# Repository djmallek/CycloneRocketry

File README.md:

# Cyclone Rocketry

This is an avionics control board for Iowa State's Cyclone Rocketry club. Our rocketry must carry a payload to a target altitude of 10,000ft.  Score is determined by how close a team's rocket can get to the target altitude, among other things.  To ensure we hit our target altitude, we have an air brakes system which actively calculates when and how long it needs to deploy it's air brakes system.  The board additionally provides data-logging and radio-relayed GPS tracking.

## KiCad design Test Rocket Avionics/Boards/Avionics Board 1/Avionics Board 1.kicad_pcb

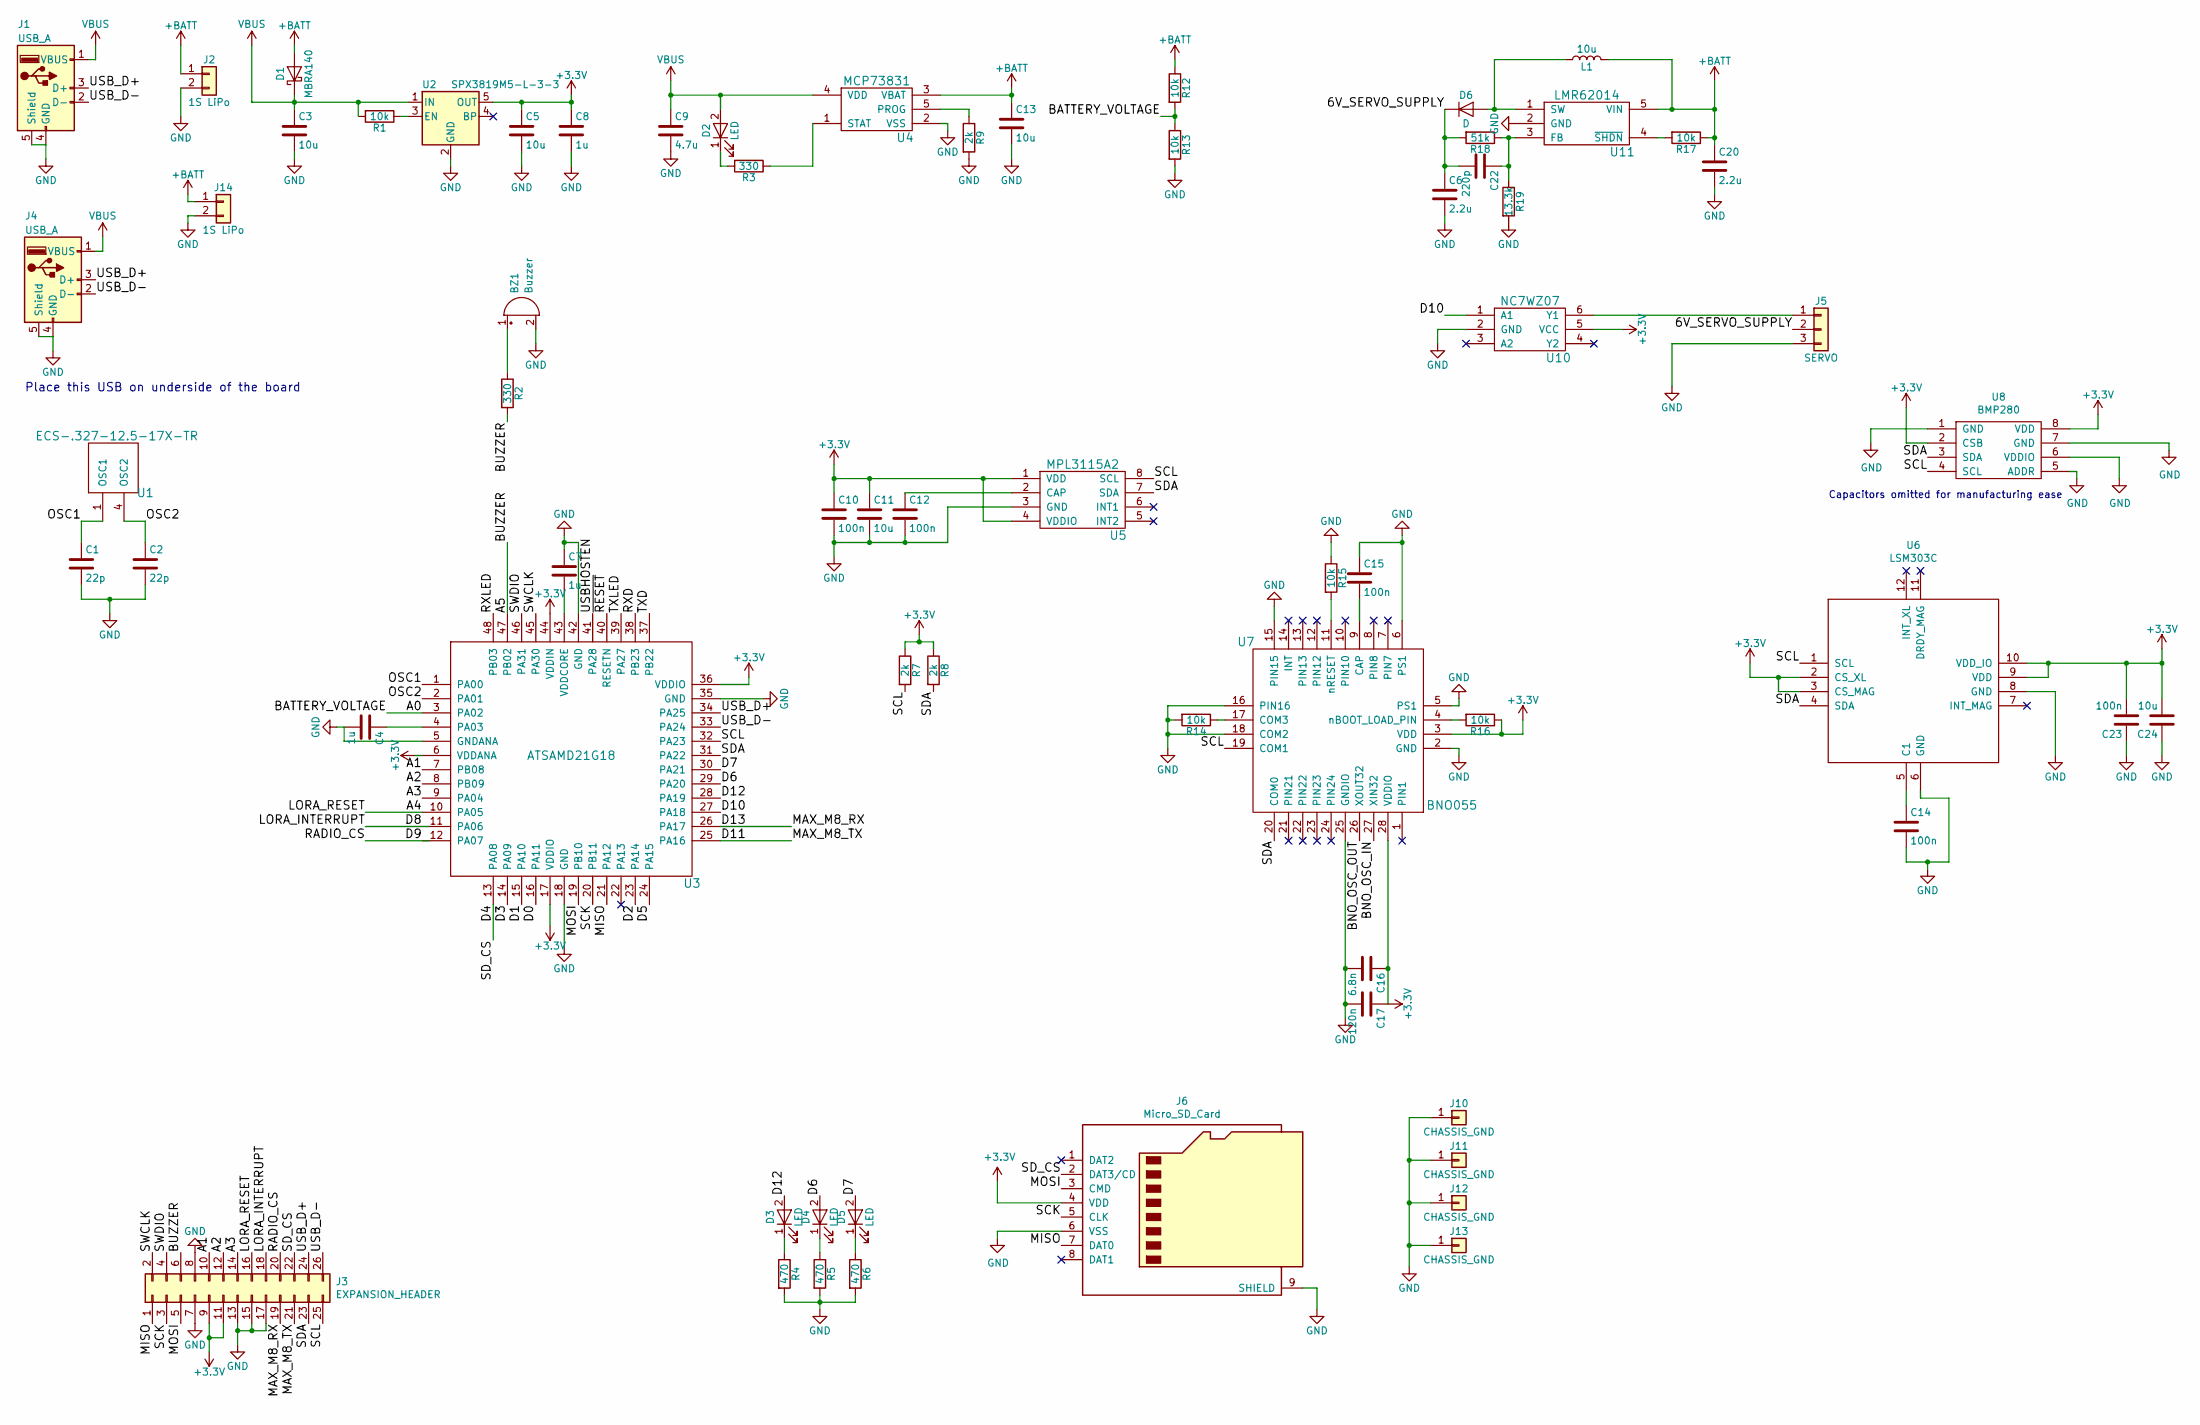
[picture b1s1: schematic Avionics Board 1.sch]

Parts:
BZ1: Buzzer; CUI_CMT-5023S-SMT
C1, C2: 22p; C_0805
C3, C5, C11, C13, C24: 10u; C_1206
C4, C7, C8: 1u; C_0805
C6, C20: 2.2u; C_1206
C9: 4.7u; C_1206
C10, C12, C14, C15, C23: 100n; C_0805
C16: 6.8n; C_0805
C17: 120n; C_0805
C22: 220p; C_0805
D1: MBRA140; DO-214AC
D2, D3, D4, D5: LED; D_0603
D6: D; D_SOD-123F
J1, J4: USB_A; USB_Mini-B
J2: 1S LiPo; JST-PH2
J3: EXPANSION_HEADER; Pin_Header_Straight_2x13_Pitch1.00mm
J5: SERVO; Pin_Header_Straight_1x03_Pitch2.54mm
J6: Micro_SD_Card; MicroSD_DM3D-SF
J10, J11, J12, J13: CHASSIS_GND; MountingHole_2.7mm_M2.5_Pad
J14: 1S LiPo; Pin_Header_Straight_1x02_Pitch2.54mm
L1: 10u; L_Wuerth_HCI-5040
R1, R12, R13, R14, R15, R16, R17: 10k; R_0805
R2, R3: 330; R_0805
R4, R5, R6: 470; R_0805
R7, R8, R9: 2k; R_0805
R18: 51k; R_0805
R19: 13.3k; R_0805
U1: ECS-.327-12.5-17X-TR; XC1195CT-ND
U2: SPX3819M5-L-3-3; SOT-23-5
U3: ATSAMD21G18; TQFP-48_7x7mm_Pitch0.5mm
U4: MCP73831; TSOT-23-5
U5: MPL3115A2
U6: LSM303C; LGA-12_2x2mm_Pitch0.5mm
U7: BNO055; BNO055-LGA
U8: BMP280
U10: NC7WZ07; SOT-363_SC-70-6
U11: LMR62014; SOT-23-5

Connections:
+3V3: C5.1, C8.1, C10.1, C11.1, C16.1, C17.1, C23.2, C24.2, J3.9, J3.11, J6.4 (VDD), R7.1, R8.1, R16.1, U2.5 (OUT), U3.6 (VDDANA), U3.17 (VDDIO), U3.36 (VDDIO), U3.44 (VDDIN), U5.1 (VDD), U5.4 (VDDIO), U6.2 (CS_XL), U6.3 (CS_MAG), U6.9 (VDD), U6.10 (VDD_IO), U7.3 (VDD), U7.28 (VDDIO), U8.2 (CSB), U8.8 (VDD), U10.5 (VCC)
+BATT: C13.1, C20.1, D1.2 (A), J2.1, J14.1, L1.2, R12.1, R17.1, U4.3 (VBAT), U11.5 (VIN)
/6V_SERVO_SUPPLY: C6.1, C22.2, D6.1 (K), J5.2, R18.2; also elsewhere on the board
/A0: R12.2, R13.1, U3.3 (PA02)
/A1: J3.10, U3.7 (PB08)
/A2: J3.12, U3.8 (PB09)
/A3: J3.14, U3.9 (PA04)
/A4: J3.16, U3.10 (PA05)
/A5: J3.6, R2.2, U3.47 (PB02)
/BNO_OSC_IN: U7.27 (XIN32)
/BNO_OSC_OUT: U7.26 (XOUT32)
/D0: U3.16 (PA11)
/D1: U3.15 (PA10)
/D2: U3.23 (PA14)
/D3: U3.14 (PA09)
/D4: J3.22, J6.2 (DAT3/CD), U3.13 (PA08)
/D5: U3.24 (PA15)
/D6: D4.2 (A), U3.29 (PA20)
/D7: D5.2 (A), U3.30 (PA21)
/D8: J3.18, U3.11 (PA06)
/D9: J3.20, U3.12 (PA07)
/D10: U3.27 (PA18), U10.1 (A1)
/D11: J3.21, U3.25 (PA16)
/D12: D3.2 (A), U3.28 (PA19)
/D13: J3.19, U3.26 (PA17)
/MISO: J3.1, J6.7 (DAT0), U3.21 (PA12)
/MOSI: J3.5, J6.3 (CMD), U3.19 (PB10)
/OSC1: C1.1, U1.1 (OSC1), U3.1 (PA00)
/OSC2: C2.1, U1.4 (OSC2), U3.2 (PA01)
/RXD: U3.38 (PB23)
/RXLED: U3.48 (PB03)
/SCK: J3.3, J6.5 (CLK), U3.20 (PB11)
/SCL: J3.25, R7.2, U3.32 (PA23), U5.8 (SCL), U6.1 (SCL), U7.19 (COM1), U8.4 (SCL)
/SDA: J3.23, R8.2, U3.31 (PA22), U5.7 (SDA), U6.4 (SDA), U7.20 (COM0), U8.3 (SDA)
/SWCLK: J3.2, U3.45 (PA30)
/SWDIO: J3.4, U3.46 (PA31)
/TXD: U3.37 (PB22)
/TXLED: U3.39 (PA27)
/USBHOSTEN: U3.41 (PA28)
/USB_D+: J1.3 (D+), J3.24, J4.3 (D+), U3.34 (PA25)
/USB_D-: J1.2 (D-), J3.26, J4.2 (D-), U3.33 (PA24)
/~RESET: U3.40 (RESETN)
GND: BZ1.2 (+), C1.2, C2.2, C3.2, C4.2, C5.2, C6.2, C7.1, C8.2, C9.2, C10.2, C11.2, C12.2, C13.2, C14.2, C15.1, C16.2, C17.2, C20.2, C23.1, C24.1, J1.4 (GND), J1.5 (Shield), J2.2, J3.7, J3.8, J3.13, J3.15, J3.17, J4.4 (GND), J4.5 (Shield), J5.3, J6.6 (VSS), J6.9 (SHIELD), J10.1, J11.1, J12.1, J13.1, J14.2, R4.2, R5.2, R6.2, R9.2, R13.2, R14.2, R15.1, R19.2, U2.2 (GND), U3.5 (GNDANA), U3.18 (GND), U3.35 (GND), U3.42 (GND), U4.2 (VSS), U5.3 (GND), U6.6 (GND), U6.8 (GND), U7.2 (GND), U7.5 (PS1), U7.6 (PS1), U7.15 (PIN15), U7.16 (PIN16), U7.18 (COM2), U7.25 (GNDIO), U8.1 (GND), U8.5 (ADDR), U8.6 (VDDIO), U8.7 (GND), U10.2 (GND), U11.2 (GND)
unnamed: BZ1.1 (-), R2.1
unnamed: C4.1, U3.4 (PA03)
unnamed: C7.2, U3.43 (VDDCORE)
unnamed: C12.1, U5.2 (CAP)
unnamed: C14.1, U6.5 (C1)
unnamed: C15.2, U7.9 (CAP)
unnamed 49: C22.1, R18.1, R19.1, U11.3 (FB); also elsewhere on the board
unnamed: D2.1 (K), R3.2
unnamed: D3.1 (K), R4.1
unnamed: D4.1 (K), R5.1
unnamed: D5.1 (K), R6.1
unnamed: D6.2 (A), L1.1, U11.1 (SW)
unnamed: J5.1, U10.6 (Y1)
unnamed: R1.1, U2.3 (EN)
unnamed: R3.1, U4.1 (STAT)
unnamed: R9.1, U4.5 (PROG)
unnamed: R14.1, U7.17 (COM3)
unnamed: R15.2, U7.11 (nRESET)
unnamed: R16.2, U7.4 (nBOOT_LOAD_PIN)
unnamed: R17.2, U11.4 (~SHDN)
VBUS: C3.1, C9.1, D1.1 (K), D2.2 (A), J1.1 (VBUS), J4.1 (VBUS), R1.2, U2.1 (IN), U4.4 (VDD)

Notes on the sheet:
Place this USB on underside of the board
Capacitors omitted for manufacturing ease

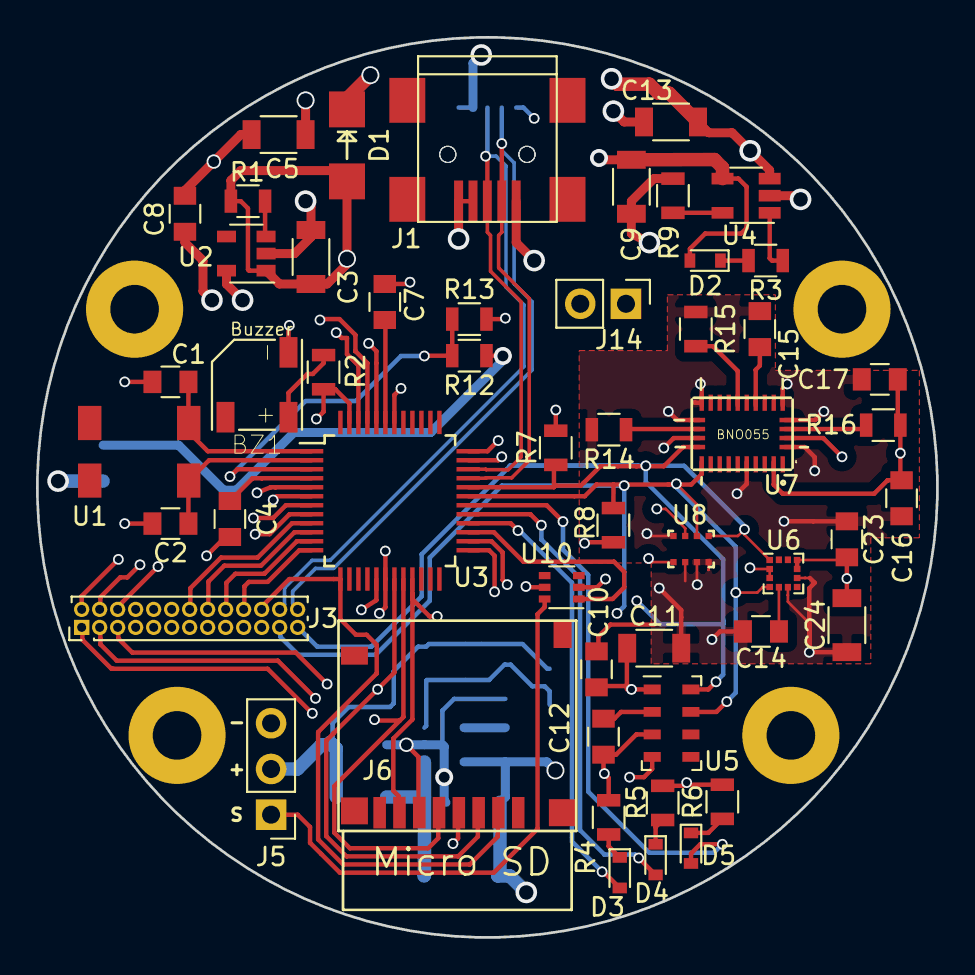
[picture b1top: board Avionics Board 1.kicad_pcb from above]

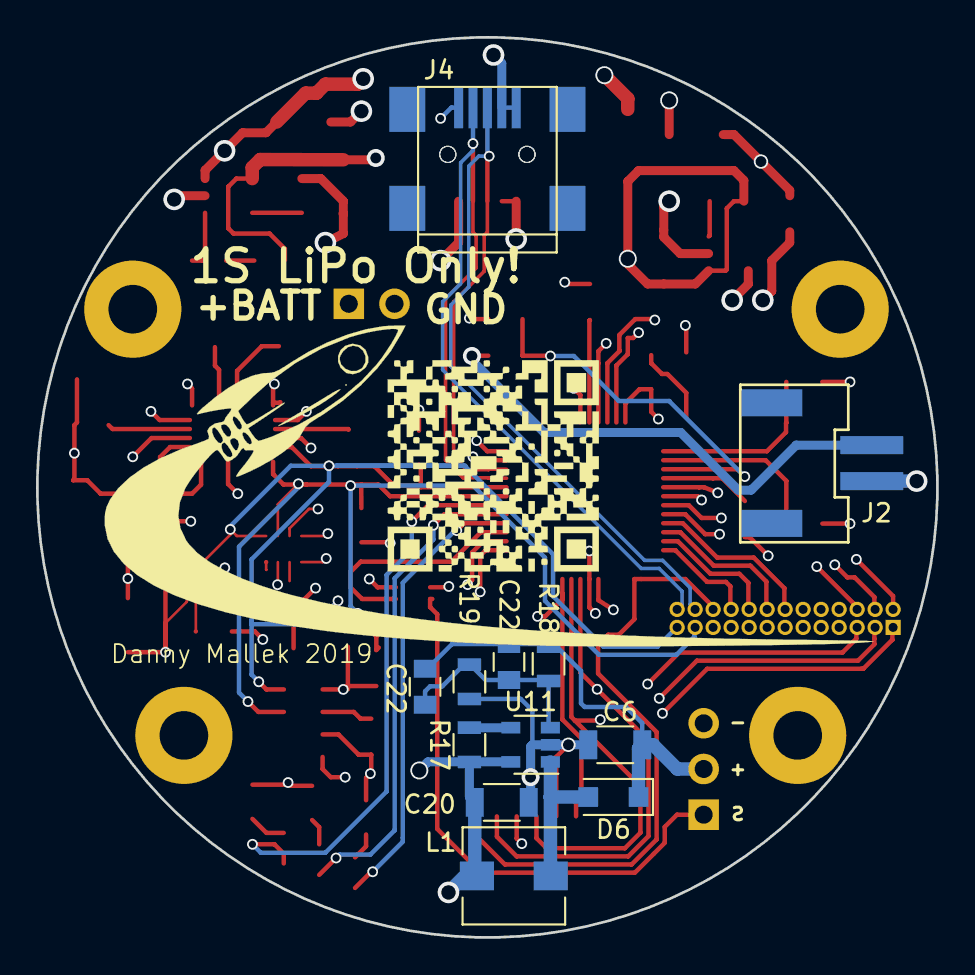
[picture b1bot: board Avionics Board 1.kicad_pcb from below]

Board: 4 copper layers, 50.0 x 50.0 mm, 68 parts (12 on the bottom side), 51 nets.

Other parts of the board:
C22#2: 220p; C_0805

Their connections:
/6V_SERVO_SUPPLY: C22#2.2; also elsewhere on the board
unnamed 49: C22#2.1; also elsewhere on the board

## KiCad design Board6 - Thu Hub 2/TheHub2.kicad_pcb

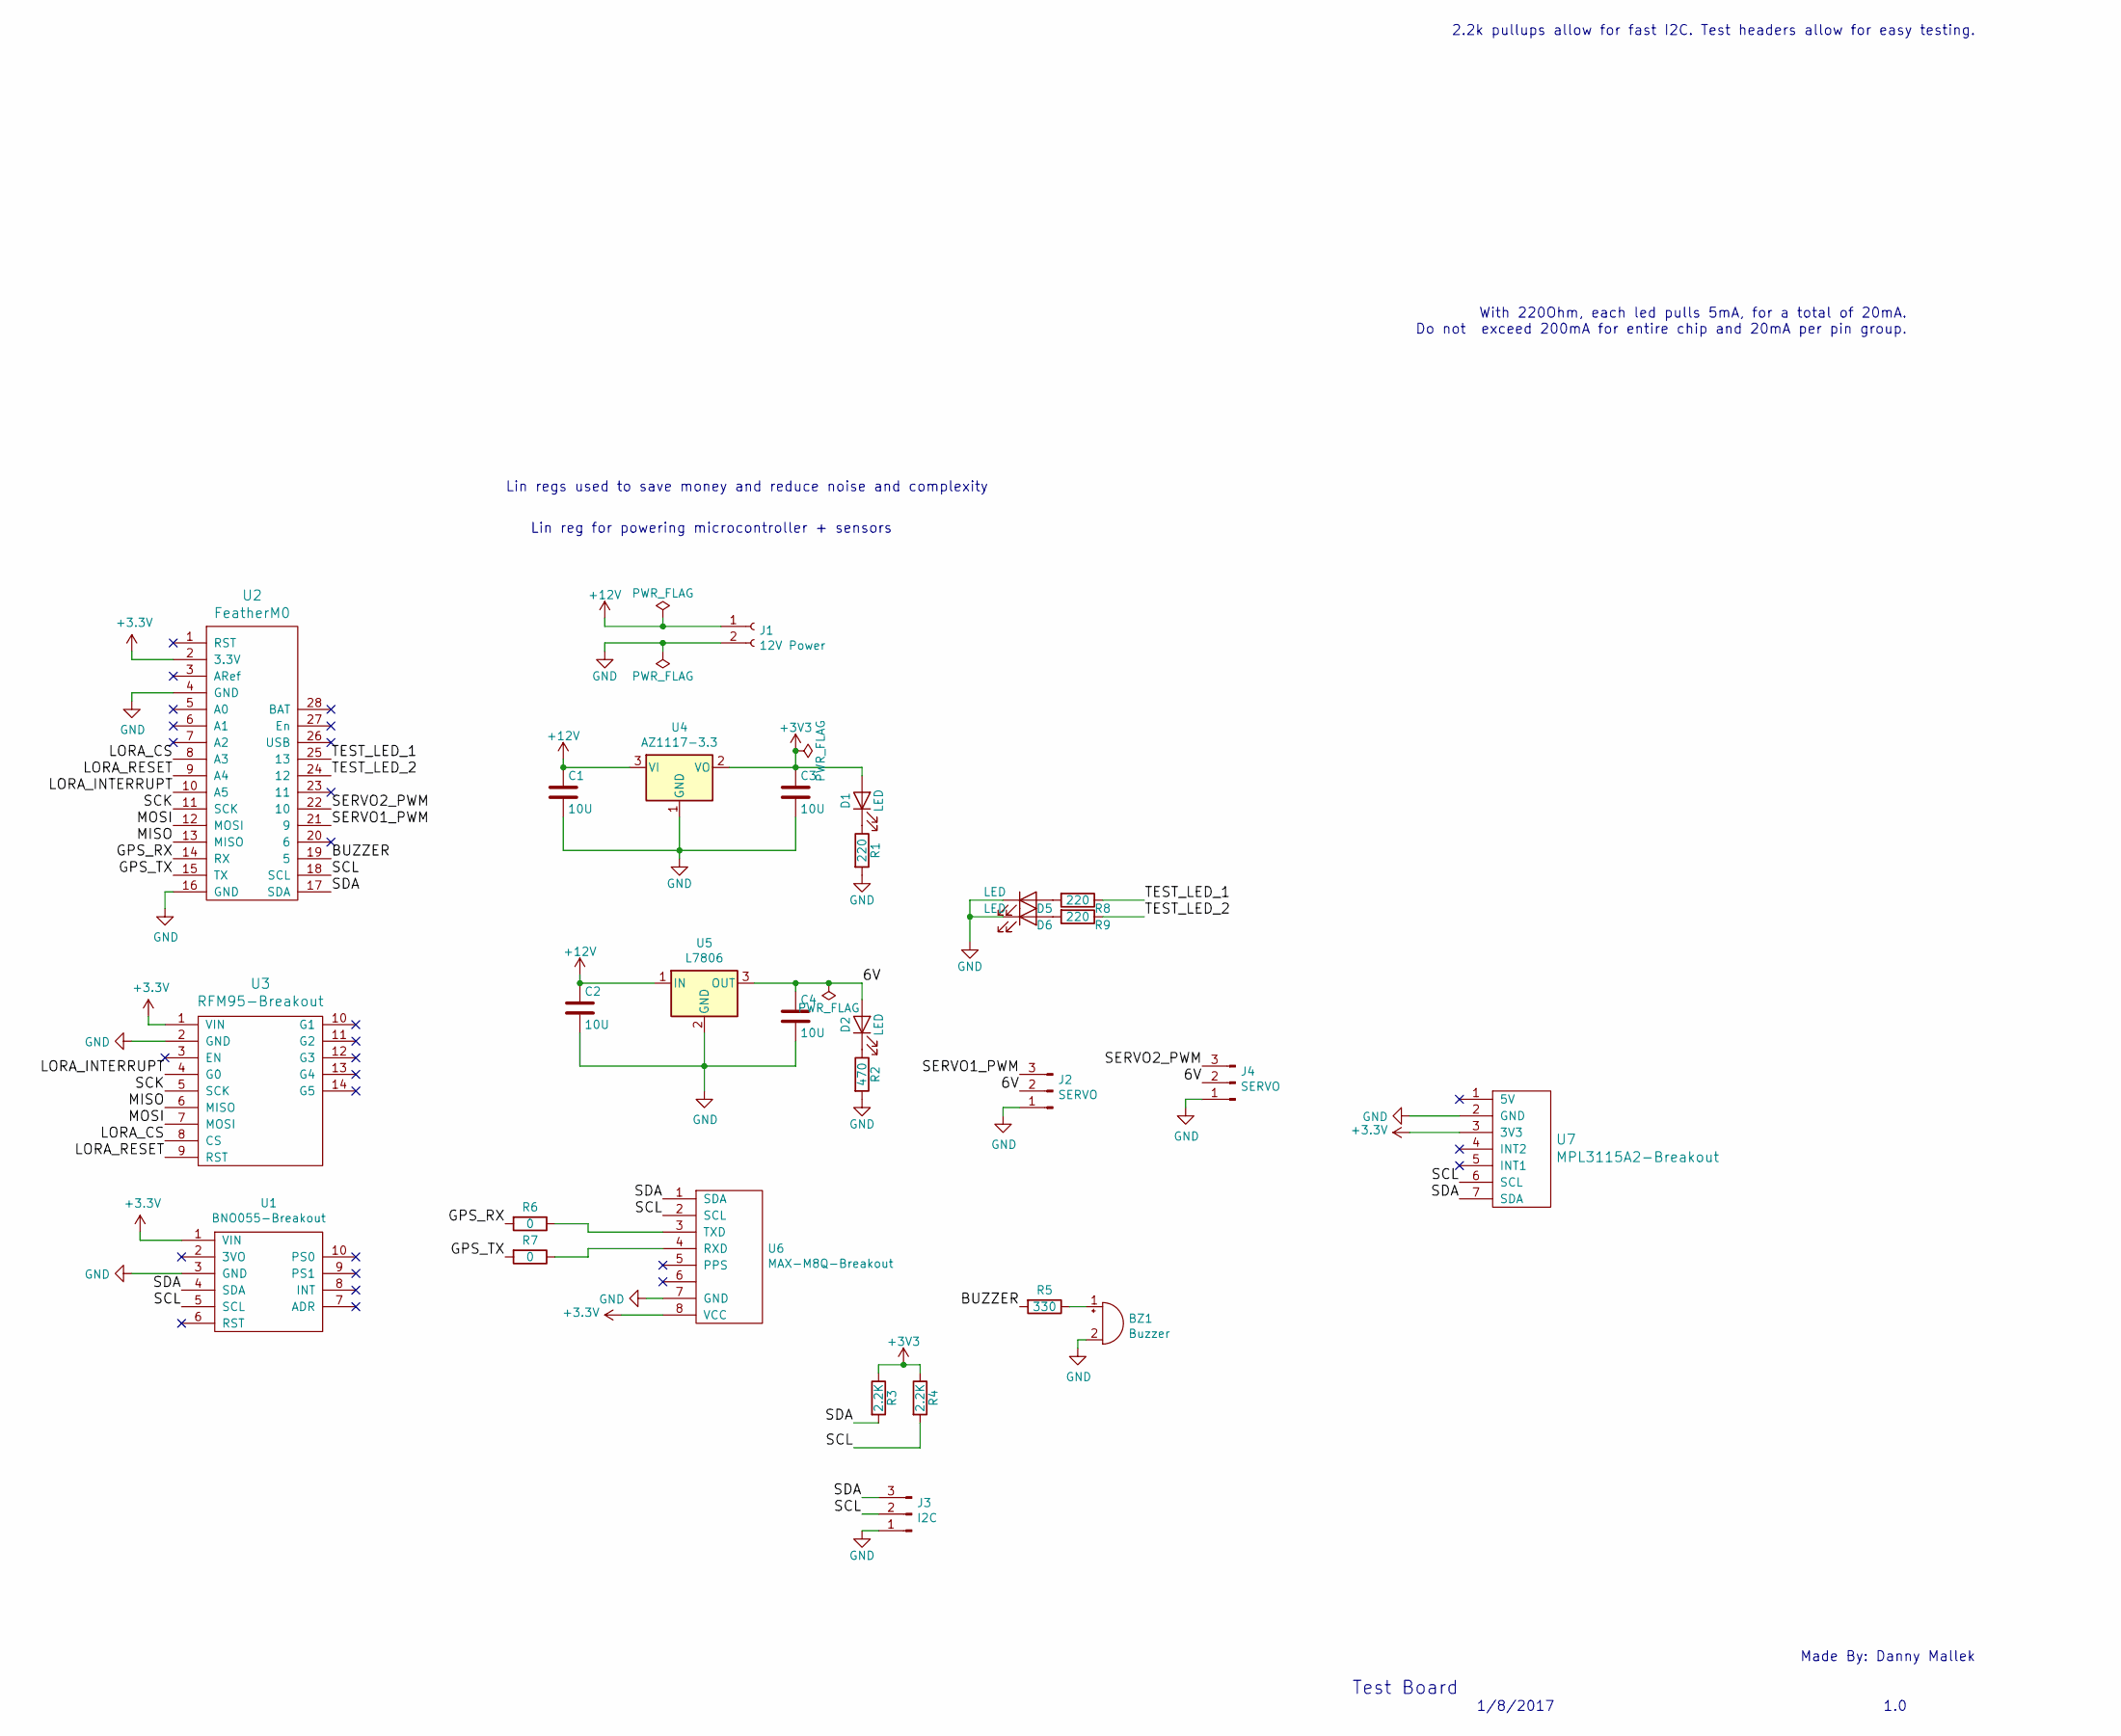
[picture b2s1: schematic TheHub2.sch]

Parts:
BZ1: Buzzer; CUI_CMT-5023S-SMT
C1, C2, C3, C4: 10U; C_0805
D1, D2, D5, D6: LED; LED_0805
J1: 12V Power; XT60
J2, J4: SERVO; Pin_Header_Straight_1x03_Pitch2.54mm
J3: I2C; Pin_Header_Straight_1x03_Pitch2.54mm
R1, R8, R9: 220; R_0805
R2: 470; R_0805
R3, R4: 2.2K; R_0805
R5: 330; R_0805
R6, R7: 0; R_0805
U1: BNO055-Breakout; BNO055
U2: FeatherM0; FEATHER-M0-DATALOGGER
U3: RFM95-Breakout
U4: AZ1117-3.3; SOT-223-3_TabPin2
U5: L7806; TO-263-2
U6: MAX-M8Q-Breakout
U7: MPL3115A2-Breakout

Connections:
+12V: C1.1, C2.1, J1.1, U4.3 (VI), U5.1 (IN)
/6V: C4.1, D2.2 (A), J2.2, J4.2, U5.3 (OUT)
/BUZZER: R5.2, U2.19 (5)
/GPS_RX: R6.2, U2.14 (RX)
/GPS_TX: R7.2, U2.15 (TX)
/LORA_CS: U2.8 (A3), U3.8 (CS)
/LORA_INTERRUPT: U2.10 (A5), U3.4 (G0)
/LORA_RESET: U2.9 (A4), U3.9 (RST)
/MISO: U2.13 (MISO), U3.6 (MISO)
/MOSI: U2.12 (MOSI), U3.7 (MOSI)
/SCK: U2.11 (SCK), U3.5 (SCK)
/SCL: J3.2, R4.2, U1.5 (SCL), U2.18 (SCL), U6.2 (SCL), U7.6 (SCL)
/SDA: J3.3, R3.2, U1.4 (SDA), U2.17 (SDA), U6.1 (SDA), U7.7 (SDA)
/SERVO1_PWM: J2.3, U2.21 (9)
/SERVO2_PWM: J4.3, U2.22 (10)
/TEST_LED_1: R8.1, U2.25 (13)
/TEST_LED_2: R9.1, U2.24 (12)
GND: BZ1.2 (+), C1.2, C2.2, C3.2, C4.2, D5.1 (K), D6.1 (K), J1.2, J2.1, J3.1, J4.1, R1.2, R2.2, U1.3 (GND), U2.4 (GND), U2.16 (GND), U3.2 (GND), U4.1 (GND), U5.2 (GND), U6.7 (GND), U7.2 (GND)
unnamed: BZ1.1 (-), R5.1
unnamed: D1.1 (K), R1.1
unnamed: D2.1 (K), R2.1
unnamed: D5.2 (A), R8.2
unnamed: D6.2 (A), R9.2
unnamed: R6.1, U6.3 (TXD)
unnamed: R7.1, U6.4 (RXD)

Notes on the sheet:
With 220Ohm, each led pulls 5mA, for a total of 20mA. Do not exceed 200mA for entire chip and 20mA per pin group.
Test Board
1.0
1/8/2017
Made By: Danny Mallek
2.2k pullups allow for fast I2C. Test headers allow for easy testing.
Lin reg for powering microcontroller + sensors
Lin regs used to save money and reduce noise and complexity

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
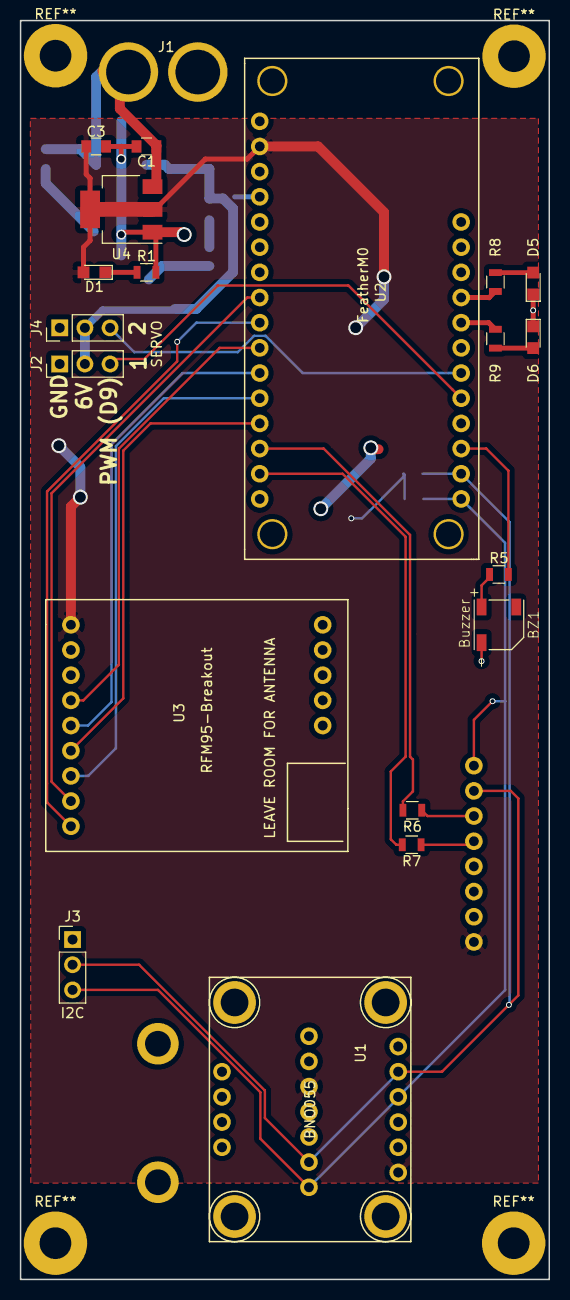
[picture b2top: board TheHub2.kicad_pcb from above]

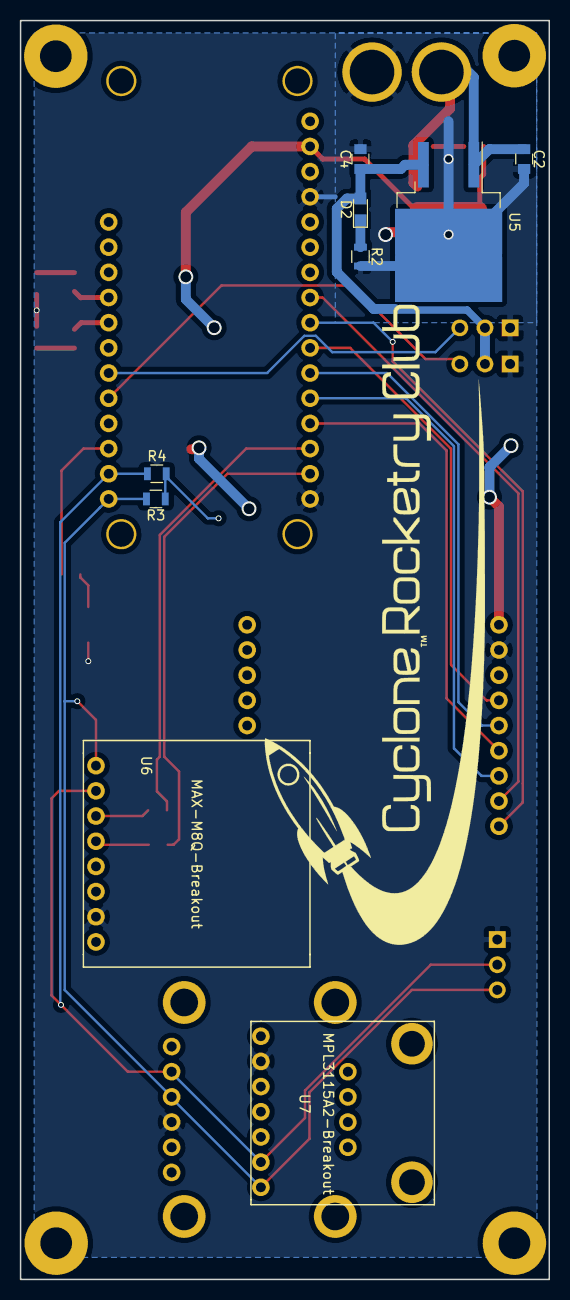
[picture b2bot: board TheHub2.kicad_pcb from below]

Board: 2 copper layers, 53.3 x 127.0 mm, 29 parts (9 on the bottom side), 26 nets.

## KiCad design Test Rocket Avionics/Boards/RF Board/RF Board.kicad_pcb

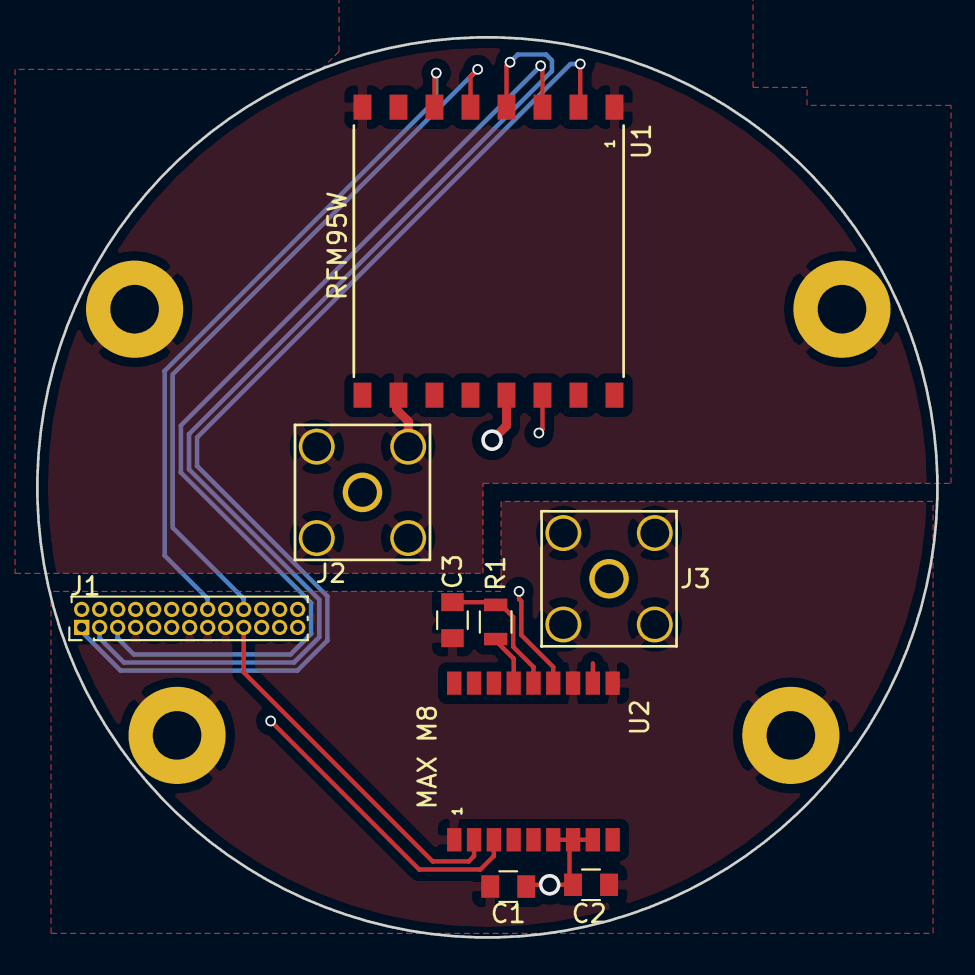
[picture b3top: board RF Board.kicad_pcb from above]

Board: 4 copper layers, 50.0 x 50.0 mm, 13 parts (0 on the bottom side), 14 nets.

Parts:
C1: 10u; C_0805
C2: 1u; C_0805
C3: 10n; C_0805
J1: EXPANSION_HEADER; Pin_Header_Straight_2x13_Pitch1.00mm
J2: LoRa; SMA_TH
J3: GPS; SMA_TH
J10, J11, J12, J13: CHASSIS_GND; MountingHole_2.7mm_M2.5_Pad
R1: 10; R_0805
U1: RFM95W
U2: MAX-M8; MAX_M82

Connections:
+3V3: C1.1, C2.1, J1.9, J1.11, U1.13, U2.6, U2.7, U2.8, U2.13
/LORA_INTERRUPT: J1.18, U1.14
/LORA_RESET: J1.16, U1.6
/MAX_M8_RX: J1.19, U2.2
/MAX_M8_TX: J1.21, U2.3
/MISO: J1.1, U1.2
/MOSI: J1.5, U1.3
/RADIO_CS: J1.20, U1.5
/SCK: J1.3, U1.4
GND: C1.2, C2.2, C3.2, J1.7, J1.8, J1.13, J1.15, J1.17, J2.2, J3.2, J10.1, J11.1, J12.1, J13.1, U1.1, U1.8, U1.10, U2.1, U2.10, U2.12
unnamed: C3.1, R1.1, U2.14
unnamed: J2.1, U1.9
unnamed: J3.1, U2.11
unnamed: R1.2, U2.15

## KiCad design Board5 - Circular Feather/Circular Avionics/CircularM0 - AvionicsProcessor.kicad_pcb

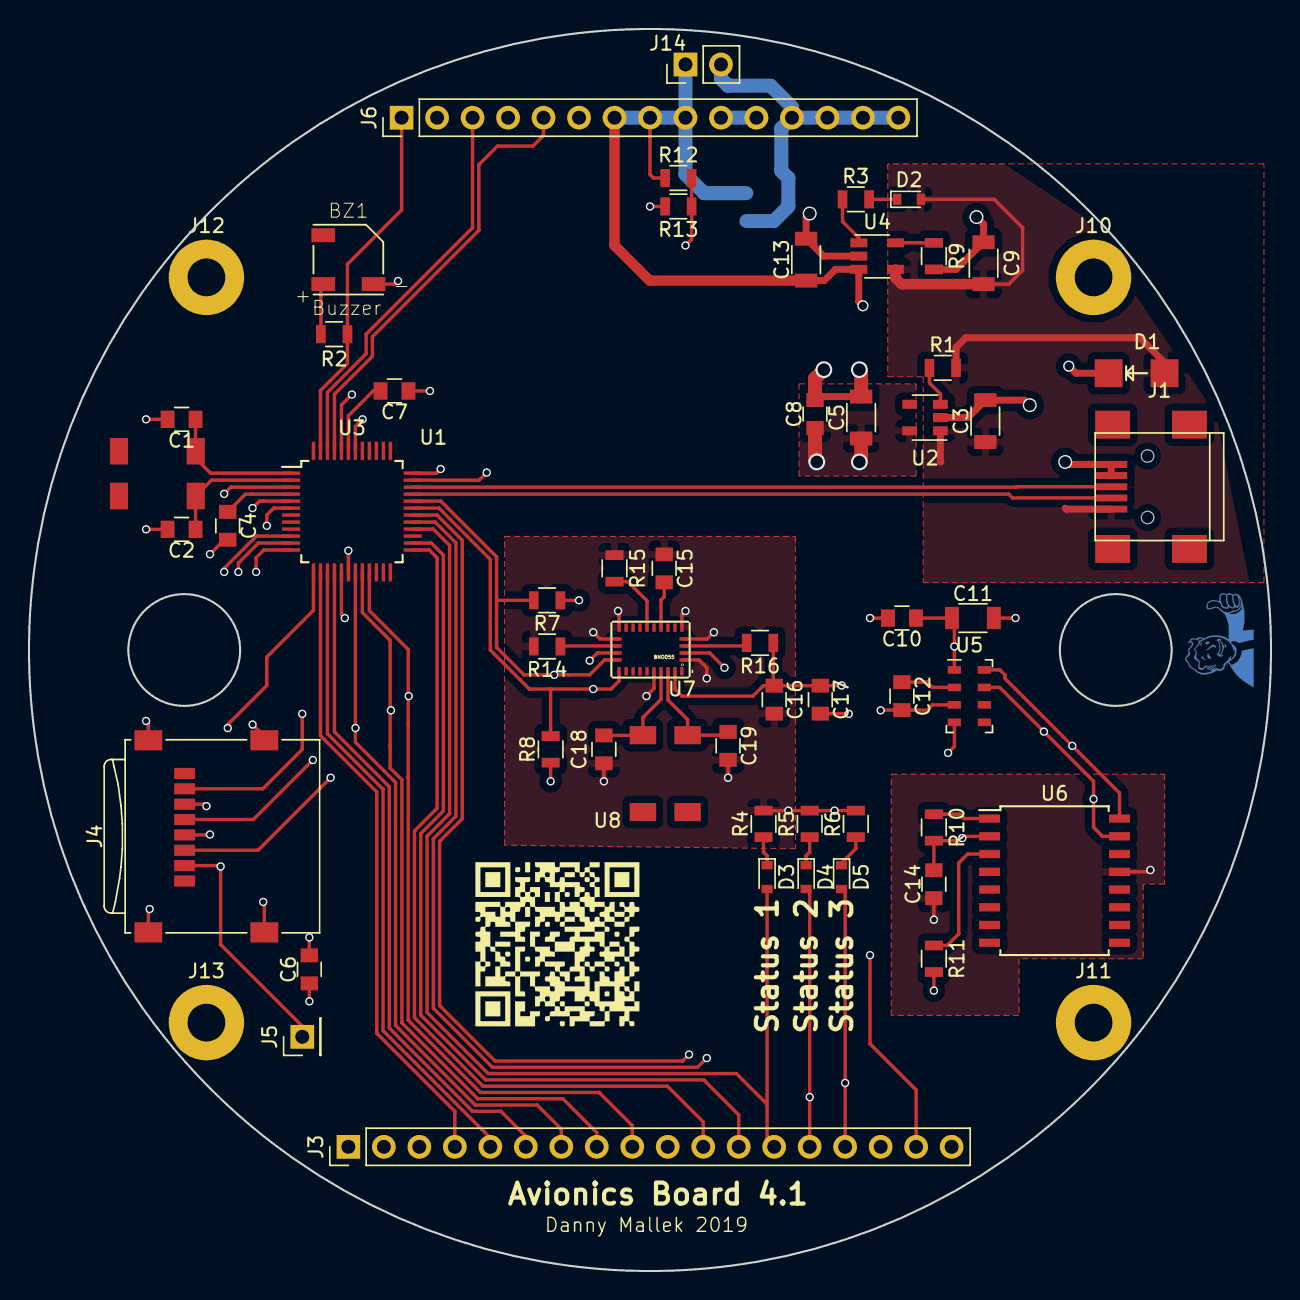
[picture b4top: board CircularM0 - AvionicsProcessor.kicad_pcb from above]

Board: 4 copper layers, 88.9 x 88.9 mm, 60 parts (1 on the bottom side), 48 nets.

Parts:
BZ1: Buzzer; CUI_CMT-5023S-SMT
C1, C2, C18, C19: 22p; C_0805
C3, C5, C11, C13: 10u; C_1206
C4, C6, C7, C8: 1u; C_0805
C9: 4.7u; C_1206
C10, C12, C15: 100n; C_0805
C14: C; C_0805
C16: 6.8n; C_0805
C17: 120n; C_0805
D1: MBRA140; DO-214AC
D2, D3, D4, D5: LED; D_0603
J1: USB_A; USB_Mini-B
J2: 1S LiPo; JST-PH2
J3: BOTTOM_HEADER; Pin_Header_Straight_1x18_Pitch2.54mm
J4: Micro_SD_Card; microSD_Card_Receptacle_Wuerth_693072010801
J5: SD_CS; Pin_Header_Straight_1x01_Pitch2.54mm
J6: TOP_HEADER; Pin_Header_Straight_1x15_Pitch2.54mm
J10, J11, J12, J13: CHASSIS_GND; MountingHole_2.7mm_M2.5_Pad
J14: 1S LiPo; Pin_Header_Straight_1x02_Pitch2.54mm
R1, R10, R11, R12, R13, R14, R15, R16: 10k; R_0805
R2, R3: 330; R_0805
R4, R5, R6: 470; R_0805
R7, R8, R9: 2k; R_0805
U1, U8: ECS-.327-12.5-17X-TR; XC1195CT-ND
U2: SPX3819M5-L-3-3; SOT-23-5
U3: ATSAMD21G18; TQFP-48_7x7mm_Pitch0.5mm
U4: MCP73831; TSOT-23-5
U5: MPL3115A2
U6: DS3231-SO16; SOIC-16W_7.5x10.3mm_Pitch1.27mm
U7: BNO055; BNO055-LGA

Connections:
+3V3: C5.1, C6.2, C8.1, C10.1, C11.1, C14.2, C16.1, C17.1, J4.4, J6.10, J6.11, R7.1, R8.1, R10.2, R11.2, R16.1, U2.5, U3.6, U3.17, U3.36, U3.44, U5.1, U5.4, U6.2, U7.3, U7.28
+BATT: C13.1, D1.2, J2.1, J6.7, J6.8, J6.9, J14.1, R12.1, U4.3
/A0: R12.2, R13.1, U3.3
/A4: J3.1, U3.10
/A5: J6.1, R2.2, U3.47
/BNO_OSC_IN: C19.1, U7.27, U8.4
/BNO_OSC_OUT: C18.1, U7.26, U8.1
/D0: J3.6, U3.16
/D1: J3.5, U3.15
/D3: J3.4, U3.14
/D4: J4.2, J5.1, U3.13
/D6: D4.2, J3.14, U3.29
/D7: D5.2, J3.15, U3.30
/D8: J3.2, U3.11
/D9: J3.3, U3.12
/D11: J3.11, U3.25
/D12: D3.2, J3.13, U3.28
/D13: J3.12, U3.26
/MISO: J3.9, J4.7, U3.21
/MOSI: J3.7, J4.3, U3.19
/OSC1: C1.1, U1.1, U3.1
/OSC2: C2.1, U1.4, U3.2
/SCK: J3.8, J4.5, U3.20
/SCL: J3.17, R7.2, U3.32, U5.8, U6.16, U7.19
/SDA: J3.16, R8.2, U3.31, U5.7, U6.15, U7.20
/SWCLK: J6.5, U3.45
/SWDIO: J6.3, U3.46
/USB_D+: J1.3, U3.34
/USB_D-: J1.2, U3.33
GND: BZ1.2, C1.2, C2.2, C3.2, C4.2, C5.2, C6.1, C7.1, C8.2, C9.2, C10.2, C11.2, C12.2, C13.2, C14.1, C15.1, C16.2, C17.2, C18.2, C19.2, J1.4, J1.5, J2.2, J3.10, J3.18, J4.6, J4.9, J6.2, J6.4, J6.6, J6.12, J6.13, J6.14, J6.15, J10.1, J11.1, J12.1, J13.1, J14.2, R4.2, R5.2, R6.2, R9.2, R13.2, R14.2, R15.1, U2.2, U3.5, U3.18, U3.35, U3.42, U4.2, U5.3, U6.13, U7.2, U7.5, U7.6, U7.15, U7.16, U7.18, U7.25
unnamed: BZ1.1, R2.1
unnamed: C4.1, U3.4
unnamed: C7.2, U3.43
unnamed: C12.1, U5.2
unnamed: C15.2, U7.9
unnamed: D2.1, R3.2
unnamed: D3.1, R4.1
unnamed: D4.1, R5.1
unnamed: D5.1, R6.1
unnamed: R1.1, U2.3
unnamed: R3.1, U4.1
unnamed: R9.1, U4.5
unnamed: R10.1, U6.1
unnamed: R11.1, U6.3
unnamed: R14.1, U7.17
unnamed: R15.2, U7.11
unnamed: R16.2, U7.4
VBUS: C3.1, C9.1, D1.1, D2.2, J1.1, R1.2, U2.1, U4.4
